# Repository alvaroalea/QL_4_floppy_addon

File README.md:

# 4 DISC DRIVE ADAPTER FOR MIRACLE DISC INTERFACE.

(C) 2023 Alvaro Alea Fernandez

License under: CERN Open Hardware Licence Version 2 - Strongly Reciprocal

https://ohwr.org/cern_ohl_s_v2.txt

This board has been reverse engineered from pictures.

THIS BOARD HAS NOT BEEN TESTED!! Use at your own risk.

## Information

This adapter is intended to connect 4 disc drives to one interface disc on the Sinclair QL Computer.

You need 2 pair of disc drives, with plain cables, on each par one drive shall be configured as DS0 and the another as DS1

The drives conected to the middle conector will be FLP1 and FLP2, and the drives conected to the outher conector will be FLP3 and FLP4

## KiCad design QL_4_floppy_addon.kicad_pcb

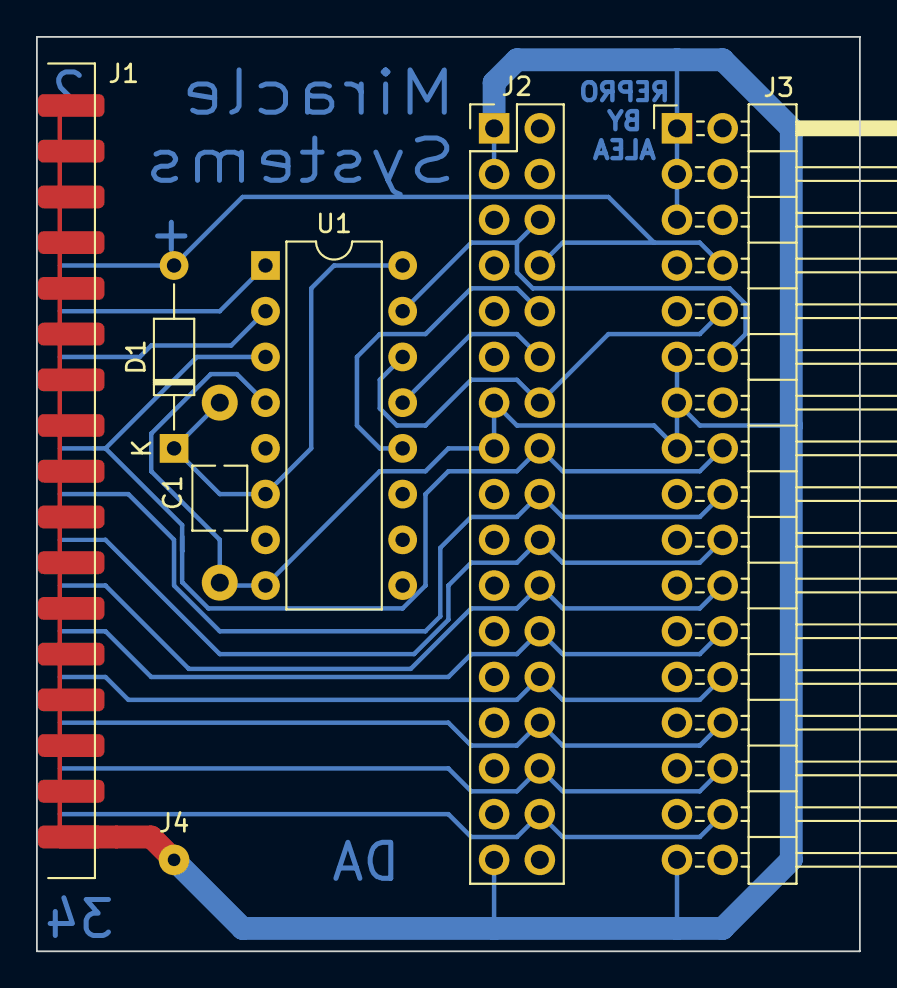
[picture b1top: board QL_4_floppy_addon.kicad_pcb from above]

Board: 2 copper layers, 45.7 x 50.8 mm, 7 parts (0 on the bottom side), 18 nets.

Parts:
C1: C; C_Disc_D7.5mm_W5.0mm_P10.00mm
D1: 1N4148; D_DO-35_SOD27_P10.16mm_Horizontal
J1: Conn_02x17_Odd_Even; DIL_Cable_Female__2x17_P2.54mm_Horizontal_PCB_edge
J2: Conn_02x17_Odd_Even; PinHeader_2x17_P2.54mm_Vertical
J3: Conn_02x17_Odd_Even; PinHeader_2x17_P2.54mm_Horizontal
J4: Conn_01x01; SolderWire-0.127sqmm_1x01_D0.48mm_OD1mm
U1: 74LS138; DIP-16_W7.62mm

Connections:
/DATA_WR: J1.22, J2.22, J3.22
/DIR: J1.18, J2.18, J3.18
/DS0: J2.10, U1.12 (O3)
/DS0T: J1.10, U1.1 (A0)
/DS1: J2.12, U1.13 (O2)
/DS1T: J1.12, U1.2 (A1)
/DS2: J2.14, J3.10, U1.14 (O1)
/DS3: J2.6, J3.12, U1.15 (O0)
/FDC_IP: D1.2 (A), J1.8, J2.8, J3.8
/FDC_RD: J1.30, J2.30, J3.30
/FDC_T0: J1.26, J2.26, J3.26
/FDC_WPRT: J1.28, J2.28, J3.28
/GATE_WR: J1.24, J2.24, J3.24
/HEAD: J1.32, J2.32, J3.32
/MOTOR_ON: J1.16, J2.16, J3.16, U1.3 (A2)
/STEP: J1.20, J2.20, J3.20
GND: C1.2, J1.1, J1.3, J1.5, J1.7, J1.9, J1.11, J1.13, J1.15, J1.17, J1.19, J1.21, J1.23, J1.25, J1.27, J1.29, J1.31, J1.33, J2.1, J2.3, J2.13, J2.15, J2.33, J3.1, J3.3, J3.5, J3.11, J3.13, J3.15, J3.33, J4.1, U1.4 (E1), U1.8 (GND)
unnamed: C1.1, D1.1 (K), U1.6 (E3), U1.16 (VCC)

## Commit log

2024-01-16 Add (good) gerber files
2024-11-22 minor typos
